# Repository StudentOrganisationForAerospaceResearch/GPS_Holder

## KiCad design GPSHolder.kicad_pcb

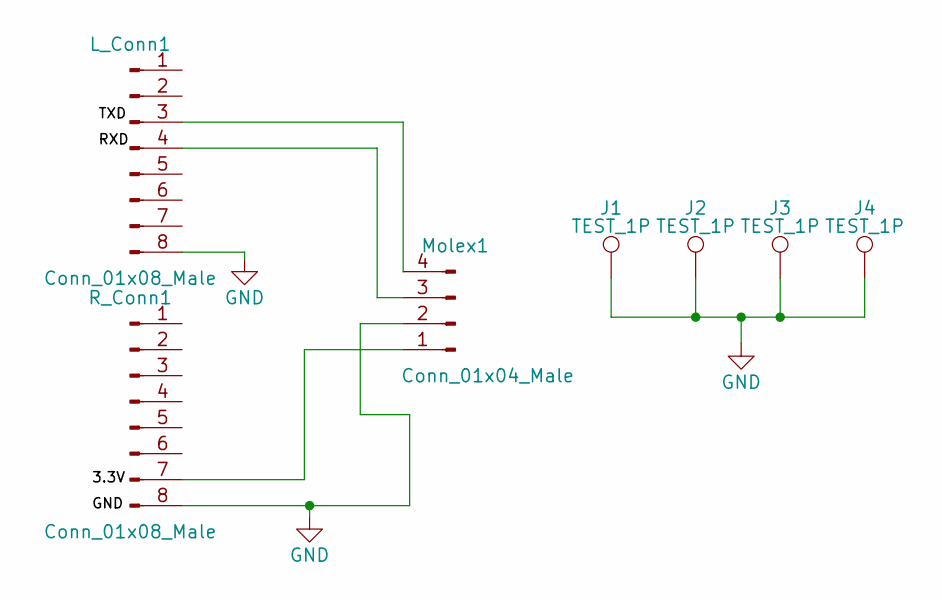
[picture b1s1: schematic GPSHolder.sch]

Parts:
J1, J2, J3, J4: TEST_1P; MountingHole_3.2mm_M3_Pad
L_Conn1: Conn_01x08_Male; Pin_Header_Angled_1x08_Pitch2.54mm
Molex1: Conn_01x04_Male; Molex_Micro-Fit_3.0_43045-0400_2x02_P3.00mm_Horizontal
R_Conn1: Conn_01x08_Male; Pin_Header_Angled_1x08_Pitch2.54mm

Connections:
GND: J1.1, J2.1, J3.1, J4.1, L_Conn1.8, Molex1.2, R_Conn1.8
unnamed: L_Conn1.3, Molex1.4
unnamed: L_Conn1.4, Molex1.3
unnamed: Molex1.1, R_Conn1.7

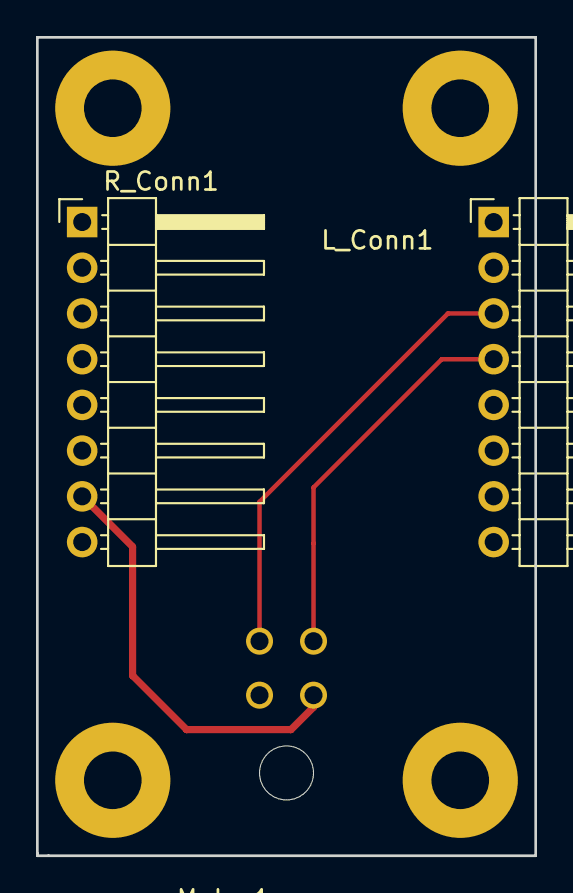
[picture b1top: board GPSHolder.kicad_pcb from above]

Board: 2 copper layers, 27.7 x 45.5 mm, 7 parts (0 on the bottom side), 4 nets.

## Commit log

2018-05-17 Final design. Schematic pdf and gerbers generated
